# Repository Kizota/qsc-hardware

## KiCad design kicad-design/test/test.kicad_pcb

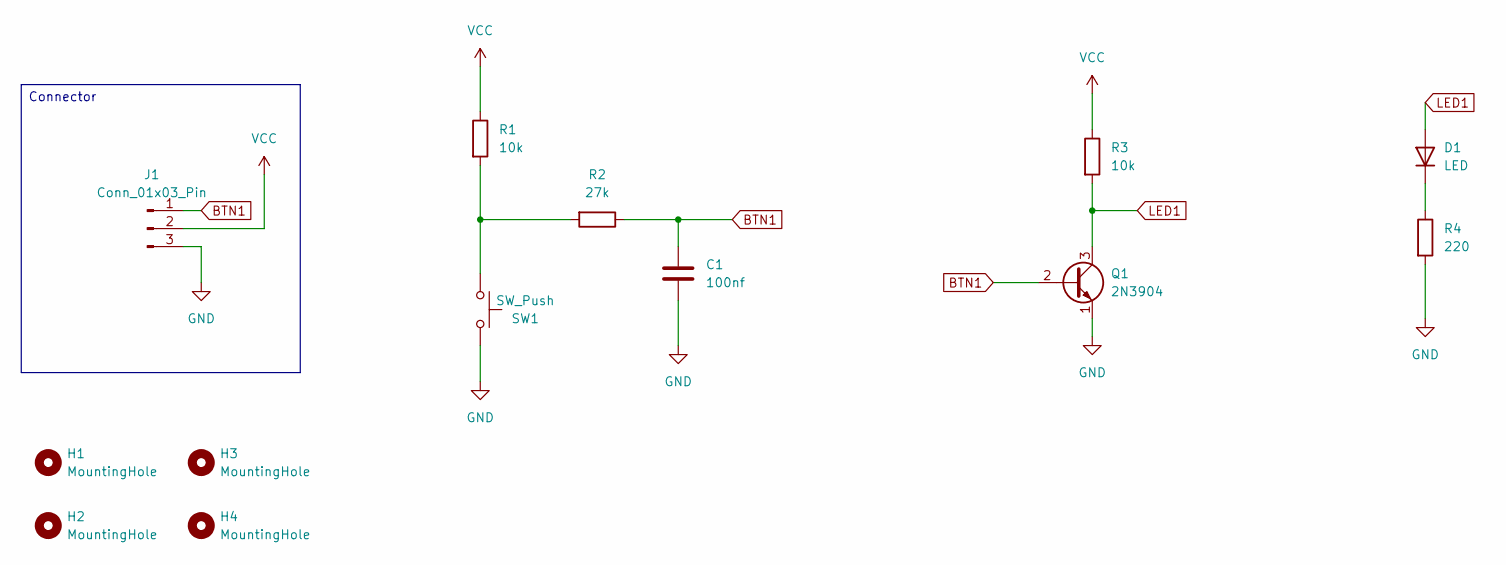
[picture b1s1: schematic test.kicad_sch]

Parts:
C1: 100nf; LED_D3.0mm
D1: LED; LED_D3.0mm
H1, H2, H3, H4: MountingHole; MountingHole_3.2mm_M3
J1: Conn_01x03_Pin; PinHeader_1x03_P2.54mm_Horizontal
Q1: 2N3904; TO-92_Inline
R1, R3: 10k; R_Axial_DIN0207_L6.3mm_D2.5mm_P10.16mm_Horizontal
R2: 27k; R_Axial_DIN0207_L6.3mm_D2.5mm_P10.16mm_Horizontal
R4: 220; R_Axial_DIN0207_L6.3mm_D2.5mm_P10.16mm_Horizontal
SW1: SW_Push; SW_PUSH_6mm_H8mm

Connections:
BTN1: C1.1, J1.1, Q1.2 (B), R2.1
GND: C1.2, J1.3, Q1.1 (E), R4.2, SW1.2
LED1: D1.2 (A), Q1.3 (C), R3.2
unnamed: D1.1 (K), R4.1
unnamed: R1.2, R2.2, SW1.1
VCC: J1.2, R1.1, R3.1

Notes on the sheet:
Connector

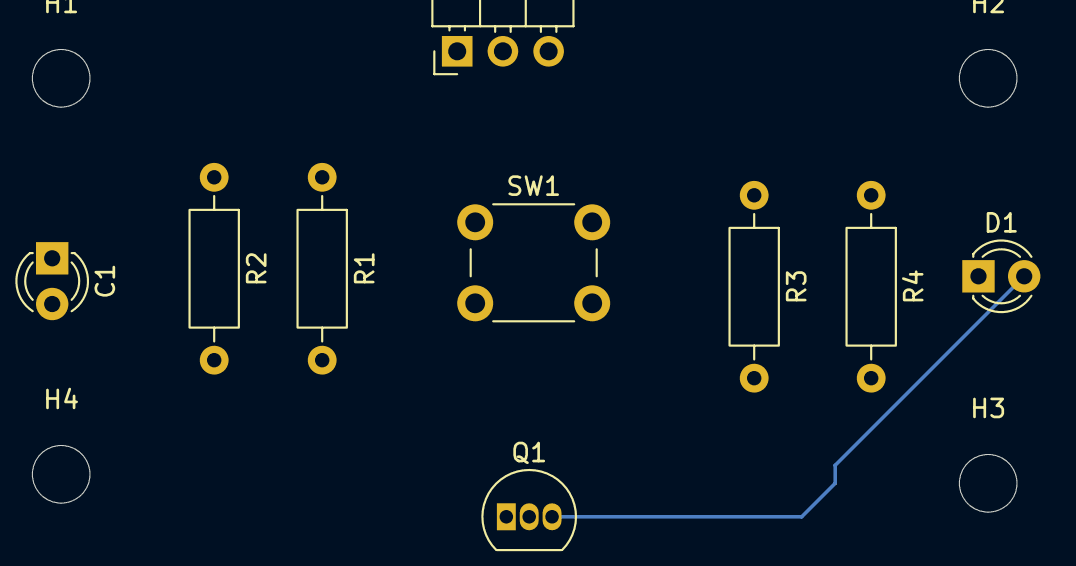
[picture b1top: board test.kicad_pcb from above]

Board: 2 copper layers, 13 parts (0 on the bottom side), 6 nets.

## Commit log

2026-01-04 intializing qsc-hardware repository
2026-01-12 Sorting some files
2026-01-12 Some more changes
